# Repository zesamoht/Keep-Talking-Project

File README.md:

# Keep-Talking-Project

A physical homage to the game Keep Talking and Nobody Explode

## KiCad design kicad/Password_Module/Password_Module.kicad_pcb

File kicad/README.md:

For Kicad drawings to be used in the physical manufacturing of the PCB

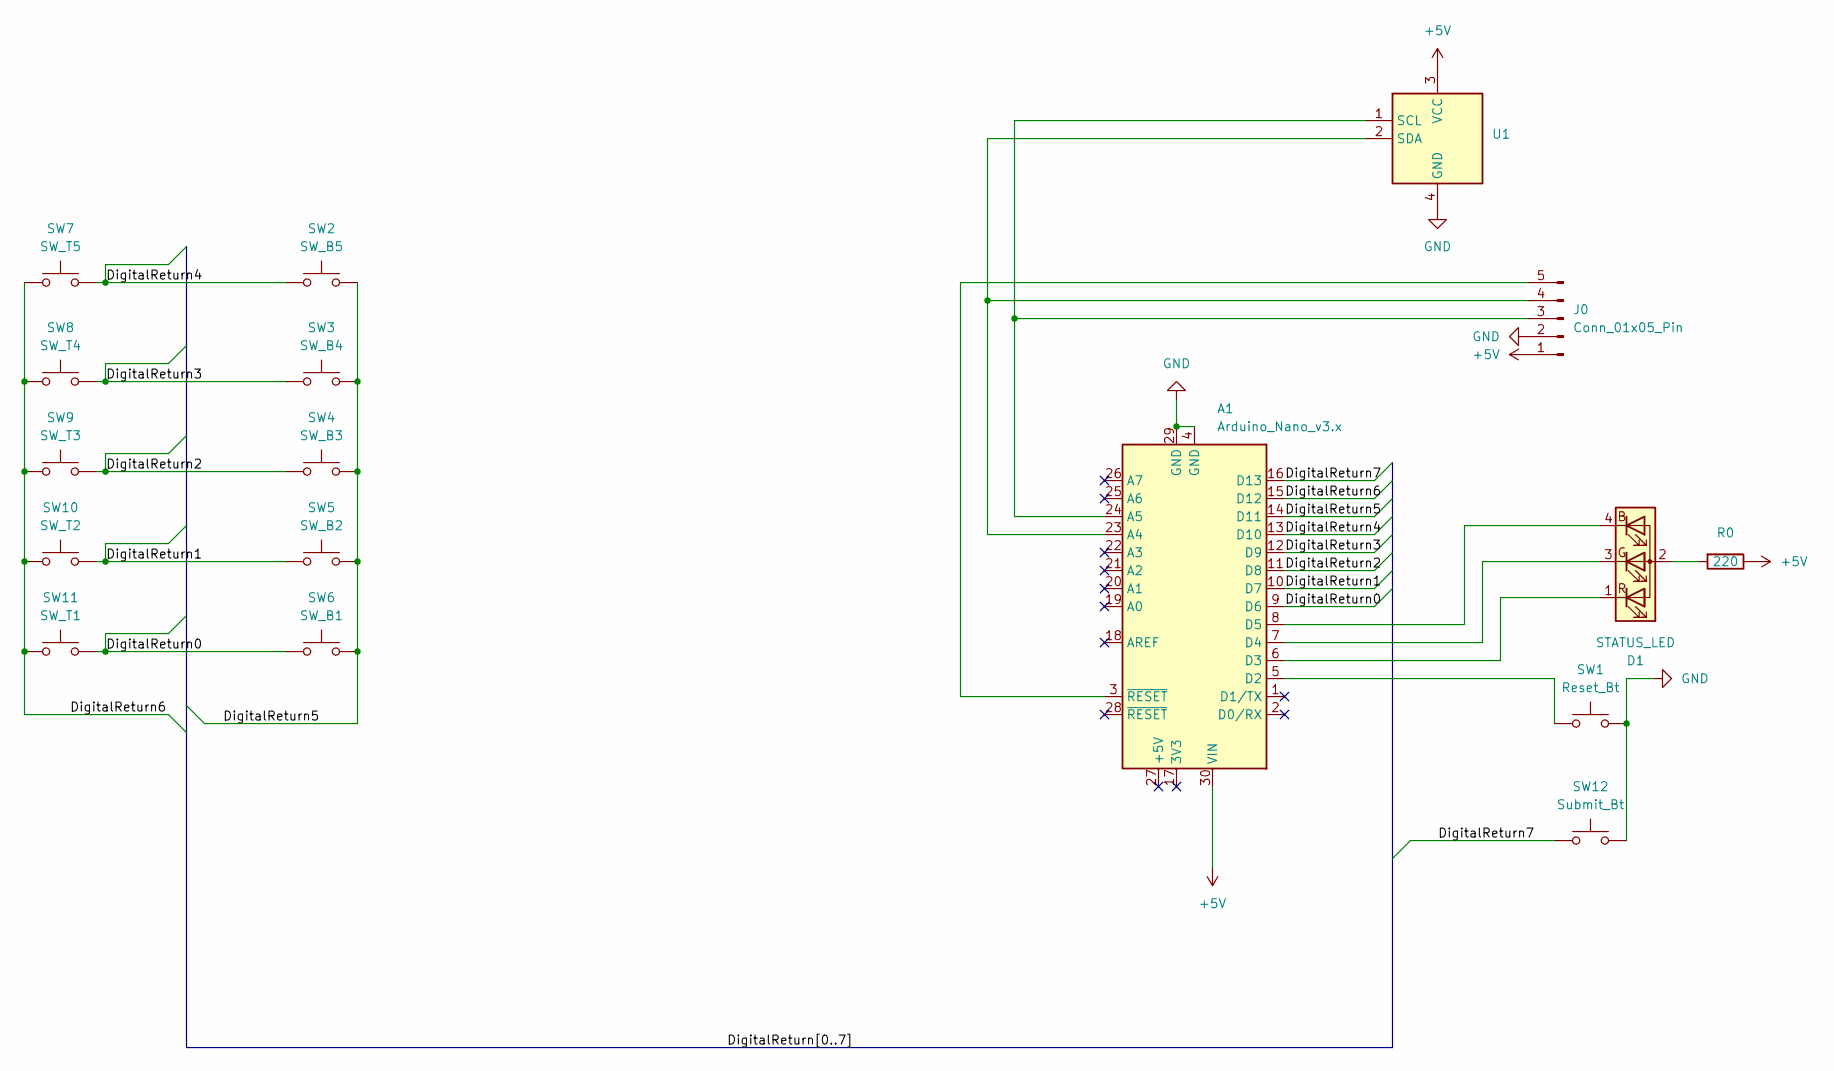
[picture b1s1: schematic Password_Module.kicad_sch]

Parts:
A1: Arduino_Nano_v3.x; Arduino_Nano
D1: STATUS_LED; LED_D5.0mm-4_RGB_Staggered_Pins
J0: Conn_01x05_Pin; JST_XH_B5B-XH-A_1x05_P2.50mm_Vertical
R0: 220; R_Axial_DIN0207_L6.3mm_D2.5mm_P7.62mm_Horizontal
SW1: Reset_Bt; SW_PUSH_6mm_H13mm
SW2: SW_B5; SW_PUSH_6mm_H13mm
SW3: SW_B4; SW_PUSH_6mm_H13mm
SW4: SW_B3; SW_PUSH_6mm_H13mm
SW5: SW_B2; SW_PUSH_6mm_H13mm
SW6: SW_B1; SW_PUSH_6mm_H13mm
SW7: SW_T5; SW_PUSH_6mm_H13mm
SW8: SW_T4; SW_PUSH_6mm_H13mm
SW9: SW_T3; SW_PUSH_6mm_H13mm
SW10: SW_T2; SW_PUSH_6mm_H13mm
SW11: SW_T1; SW_PUSH_6mm_H13mm
SW12: Submit_Bt; SW_PUSH_6mm_H13mm
U1: LCD I2C 8x2 (PCF8574T) I2C

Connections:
+5V: A1.30 (VIN), J0.1, R0.1, U1.3 (VCC)
/DigitalReturn0: A1.9 (D6), SW6.2, SW11.2
/DigitalReturn1: A1.10 (D7), SW5.2, SW10.2
/DigitalReturn2: A1.11 (D8), SW4.2, SW9.2
/DigitalReturn3: A1.12 (D9), SW3.2, SW8.2
/DigitalReturn4: A1.13 (D10), SW2.2, SW7.2
/DigitalReturn5: A1.14 (D11), SW2.1, SW3.1, SW4.1, SW5.1, SW6.1
/DigitalReturn6: A1.15 (D12), SW7.1, SW8.1, SW9.1, SW10.1, SW11.1
/DigitalReturn7: A1.16 (D13), SW12.1
GND: A1.4 (GND), A1.29 (GND), J0.2, SW1.2, SW12.2, U1.4 (GND)
unnamed: A1.23 (A4), J0.4, U1.2 (SDA)
unnamed: A1.24 (A5), J0.3, U1.1 (SCL)
unnamed: A1.5 (D2), SW1.1
unnamed: A1.6 (D3), D1.1 (RK)
unnamed: A1.7 (D4), D1.3 (GK)
unnamed: A1.8 (D5), D1.4 (BK)
unnamed: D1.2 (A), R0.2
unnamed: A1.3 (~RESET), J0.5

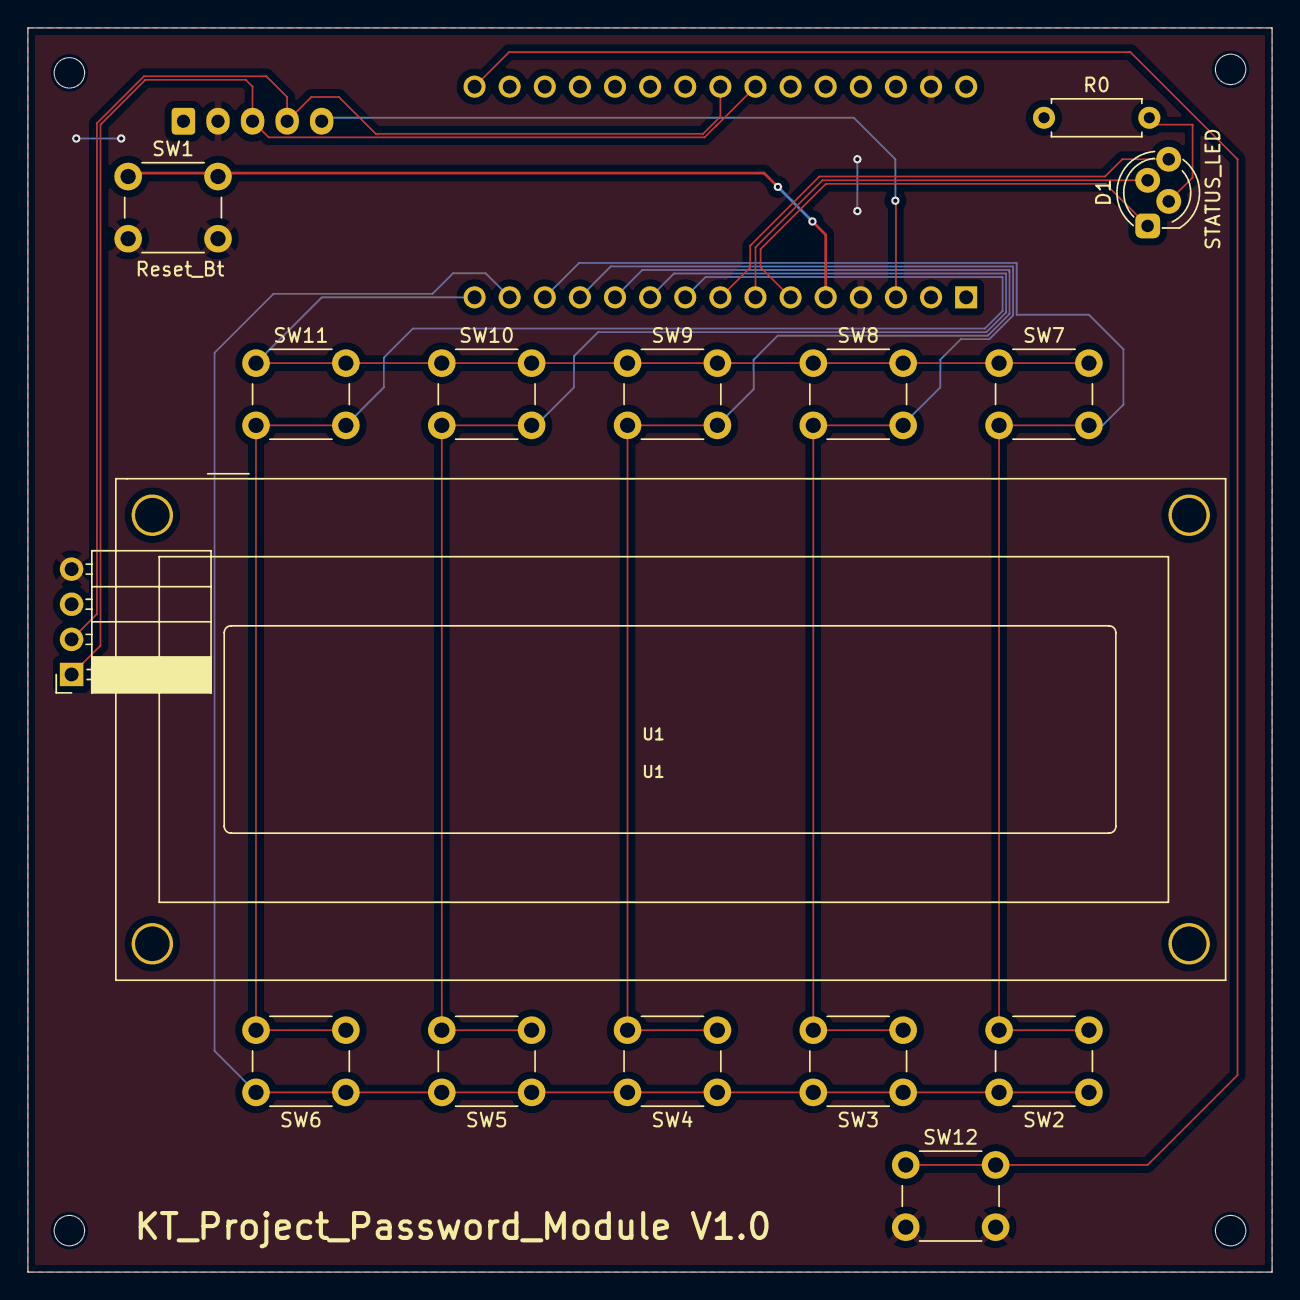
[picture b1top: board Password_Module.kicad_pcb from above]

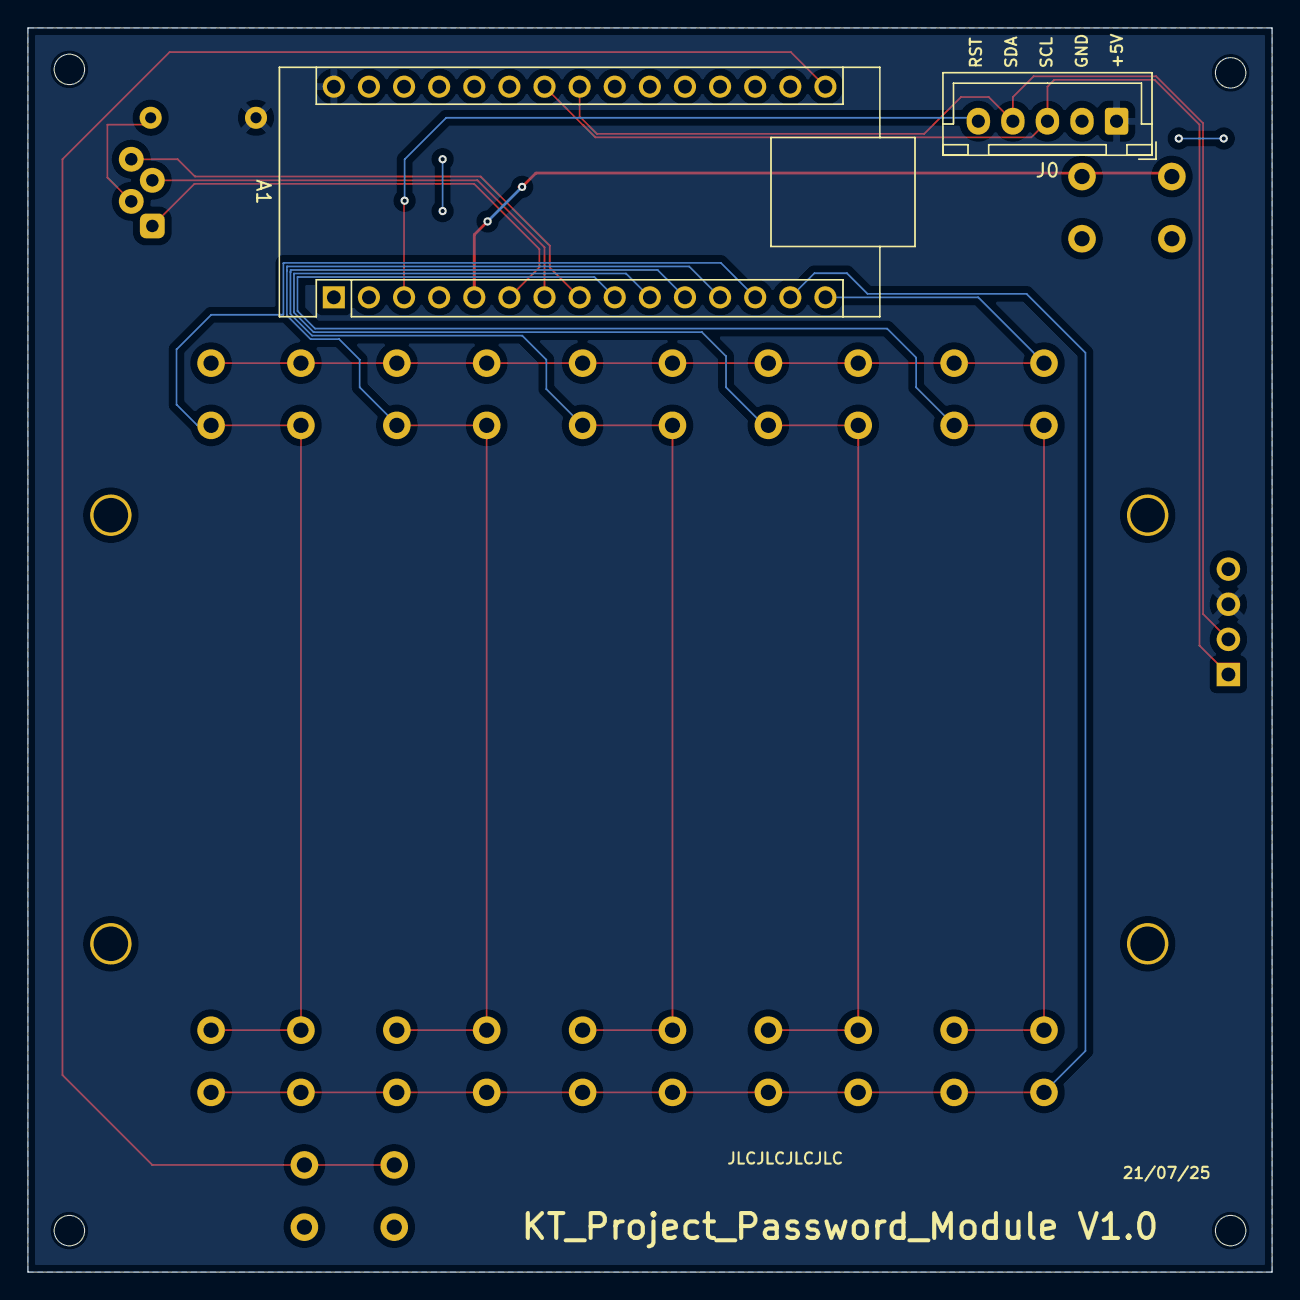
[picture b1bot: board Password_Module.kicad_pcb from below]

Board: 2 copper layers, 90.0 x 90.0 mm, 17 parts (2 on the bottom side), 18 nets.

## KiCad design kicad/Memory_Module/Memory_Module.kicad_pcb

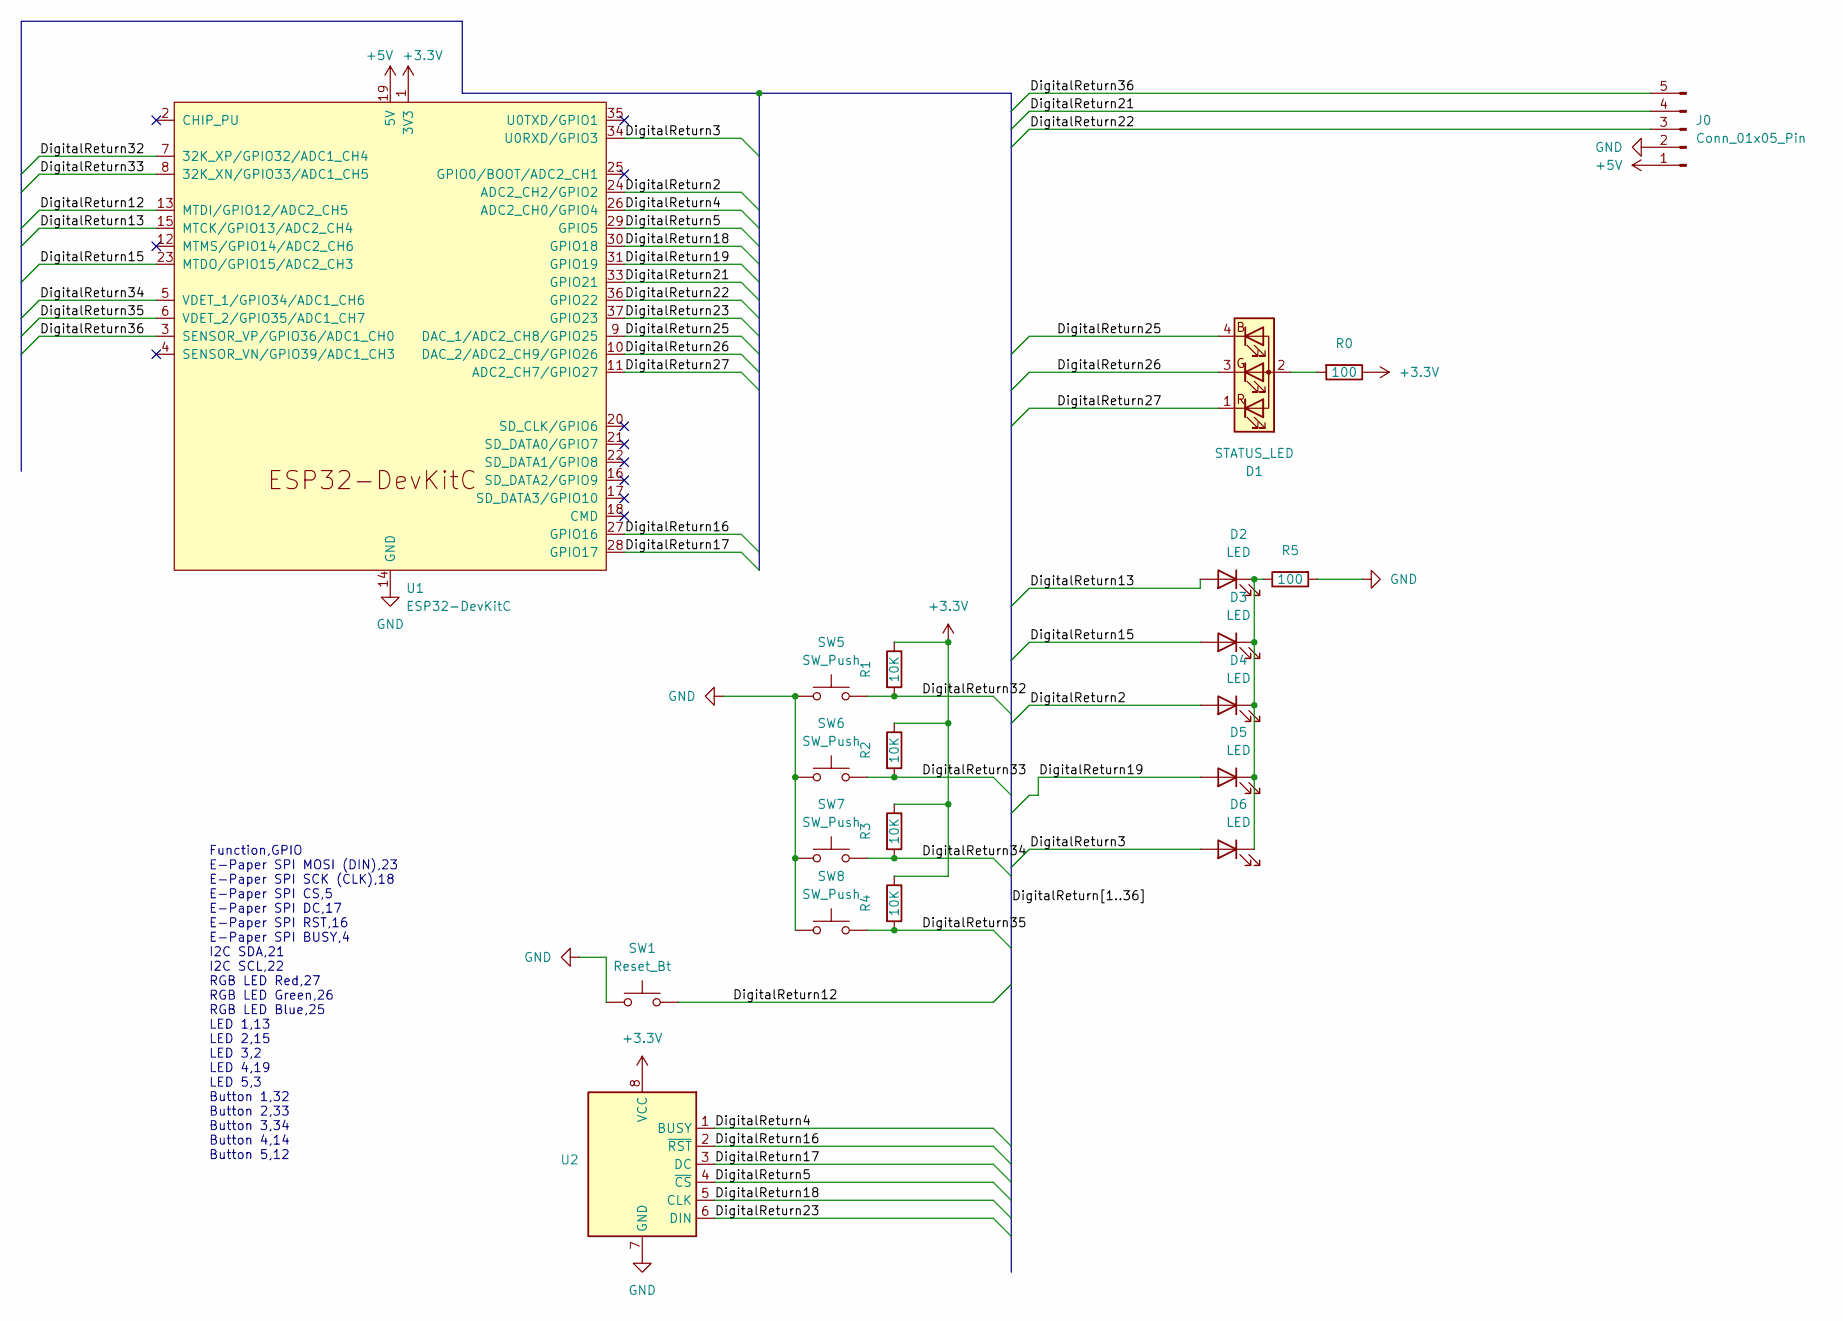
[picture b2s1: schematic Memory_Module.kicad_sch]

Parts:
D1: STATUS_LED; LED_D5.0mm-4_RGB_Staggered_Pins
D2, D3, D4, D5, D6: LED; LED_D5.0mm
J0: Conn_01x05_Pin; JST_XH_B5B-XH-A_1x05_P2.50mm_Vertical
R0, R5: 100; R_Axial_DIN0207_L6.3mm_D2.5mm_P7.62mm_Horizontal
R1, R2, R3, R4: 10K; R_Axial_DIN0207_L6.3mm_D2.5mm_P7.62mm_Horizontal
SW1: Reset_Bt; SW_PUSH_6mm_H13mm
SW5, SW6, SW7, SW8: SW_Push; SW_PUSH_6mm_H13mm
U1: ESP32-DevKitC
U2: WaveShare_E-Paper_Display_200x200

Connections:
+3.3V: R0.1, R1.1, R2.1, R3.1, R4.1, U1.1 (3V3), U2.8 (VCC)
+5V: J0.1, U1.19 (5V)
/DigitalReturn2: D4.2 (A), U1.24 (ADC2_CH2/GPIO2)
/DigitalReturn3: D6.2 (A), U1.34 (U0RXD/GPIO3)
/DigitalReturn4: U1.26 (ADC2_CH0/GPIO4), U2.1 (BUSY)
/DigitalReturn5: U1.29 (GPIO5), U2.4 (~CS)
/DigitalReturn12: SW1.1, U1.13 (MTDI/GPIO12/ADC2_CH5)
/DigitalReturn13: D2.2 (A), U1.15 (MTCK/GPIO13/ADC2_CH4)
/DigitalReturn15: D3.2 (A), U1.23 (MTDO/GPIO15/ADC2_CH3)
/DigitalReturn16: U1.27 (GPIO16), U2.2 (~RST)
/DigitalReturn17: U1.28 (GPIO17), U2.3 (DC)
/DigitalReturn18: U1.30 (GPIO18), U2.5 (CLK)
/DigitalReturn19: D5.2 (A), U1.31 (GPIO19)
/DigitalReturn21: J0.4, U1.33 (GPIO21)
/DigitalReturn22: J0.3, U1.36 (GPIO22)
/DigitalReturn23: U1.37 (GPIO23), U2.6 (DIN)
/DigitalReturn25: D1.4 (BK), U1.9 (DAC_1/ADC2_CH8/GPIO25)
/DigitalReturn26: D1.3 (GK), U1.10 (DAC_2/ADC2_CH9/GPIO26)
/DigitalReturn27: D1.1 (RK), U1.11 (ADC2_CH7/GPIO27)
/DigitalReturn32: R1.2, SW5.2, U1.7 (32K_XP/GPIO32/ADC1_CH4)
/DigitalReturn33: R2.2, SW6.2, U1.8 (32K_XN/GPIO33/ADC1_CH5)
/DigitalReturn34: R3.2, SW7.2, U1.5 (VDET_1/GPIO34/ADC1_CH6)
/DigitalReturn35: R4.2, SW8.2, U1.6 (VDET_2/GPIO35/ADC1_CH7)
/DigitalReturn36: J0.5, U1.3 (SENSOR_VP/GPIO36/ADC1_CH0)
GND: J0.2, R5.2, SW1.2, SW5.1, SW6.1, SW7.1, SW8.1, U1.14 (GND), U1.32 (GND), U1.38 (GND), U2.7 (GND)
unnamed: D1.2 (A), R0.2
unnamed: D2.1 (K), D3.1 (K), D4.1 (K), D5.1 (K), D6.1 (K), R5.1

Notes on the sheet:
Function,GPIO E-Paper SPI MOSI (DIN),23 E-Paper SPI SCK (CLK),18 E-Paper SPI CS,5 E-Paper SPI DC,17 E-Paper SPI RST,16 E-Paper SPI BUSY,4 I2C SDA,21 I2C SCL,22 RGB LED Red,27 RGB LED Green,26 RGB LED Blue,25 LED 1,13 LED 2,15 LED 3,2 LED 4,19 LED 5,3 Button 1,32 Button 2,33 Button 3,34 Button 4,14 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

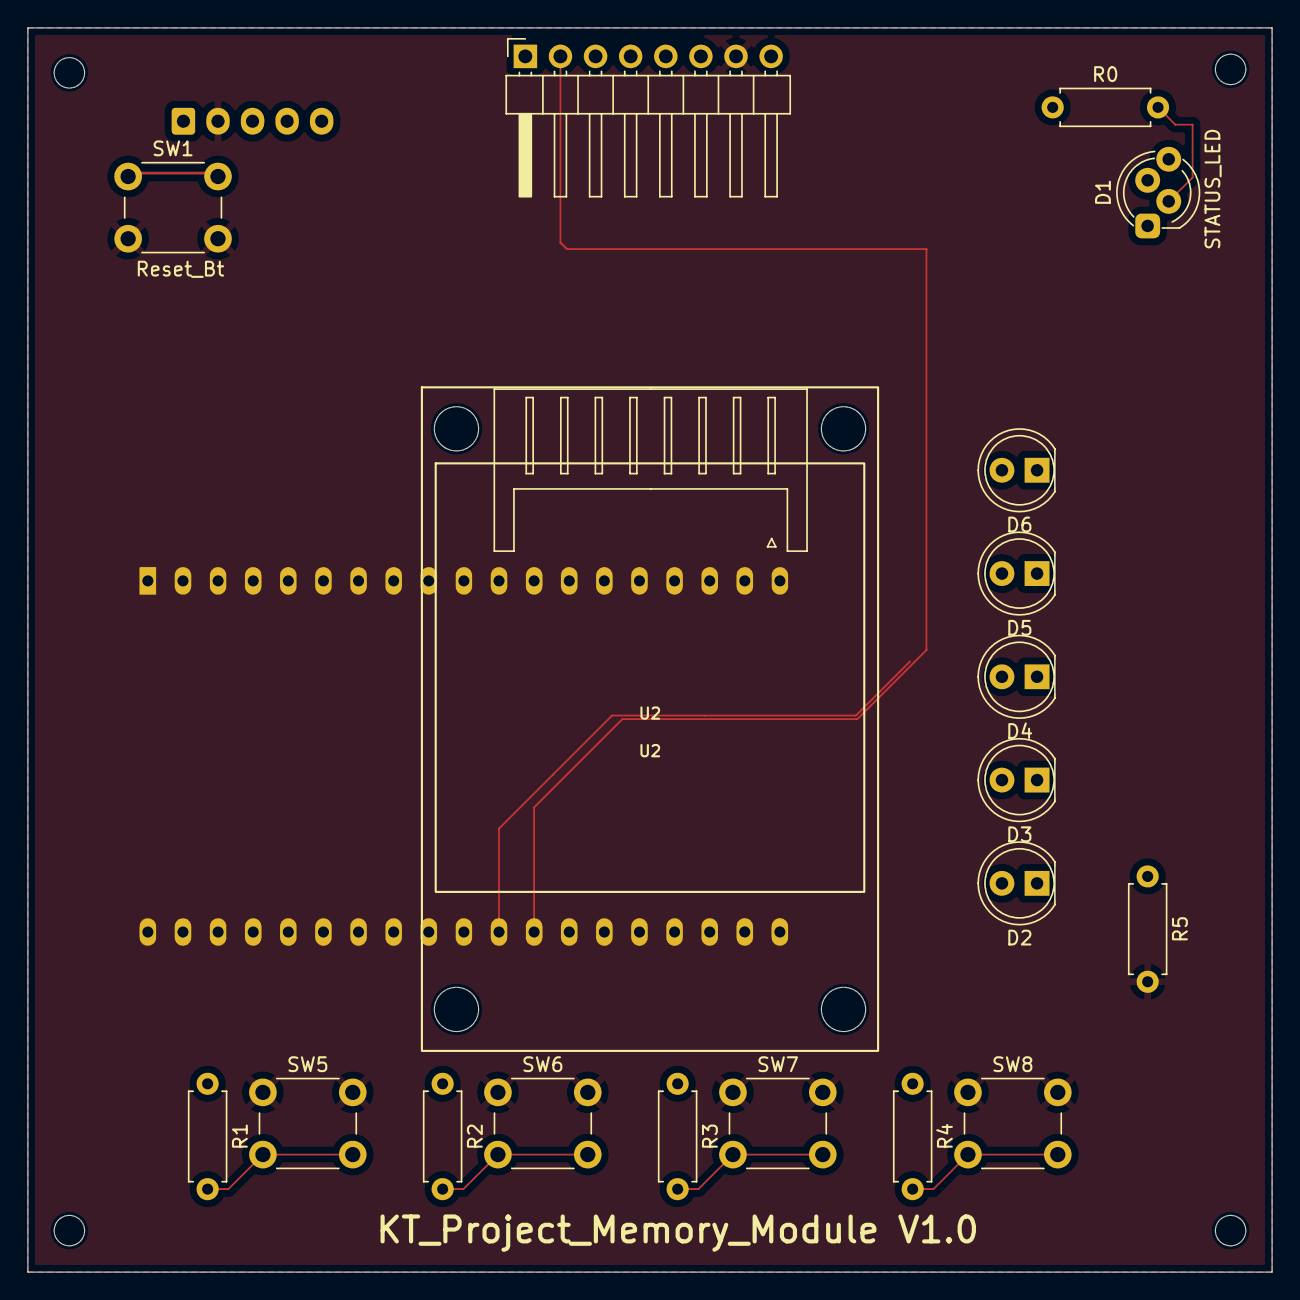
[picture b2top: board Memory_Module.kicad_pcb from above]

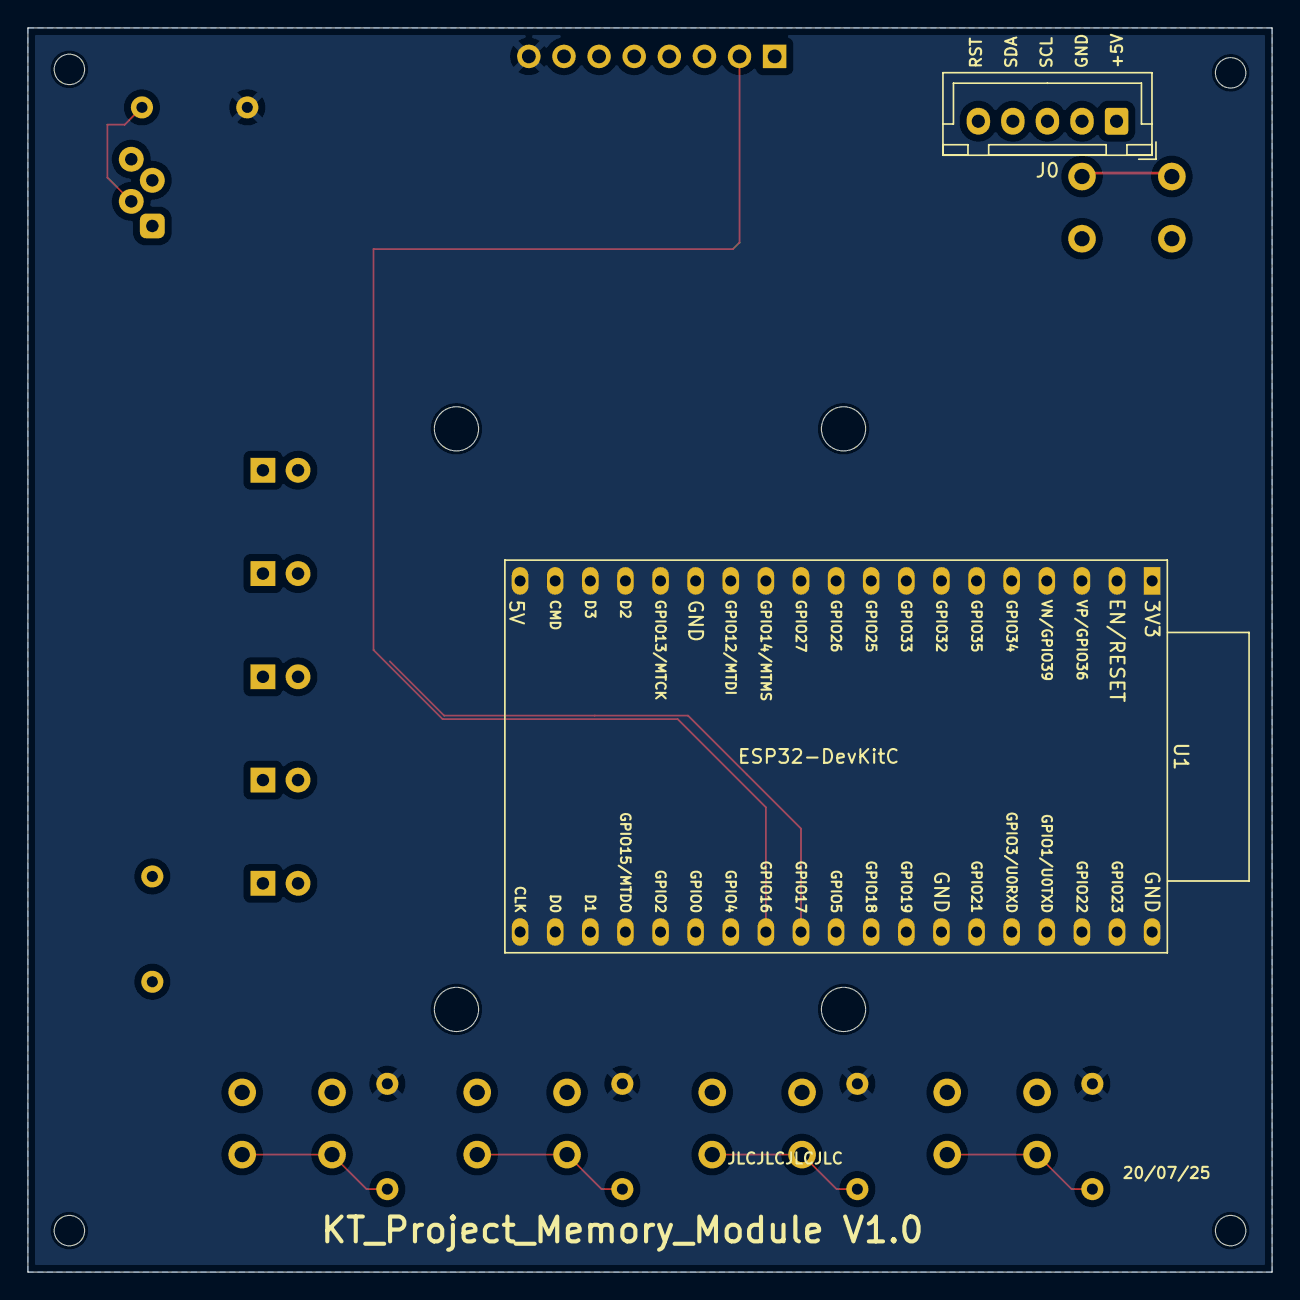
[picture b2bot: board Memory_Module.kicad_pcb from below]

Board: 2 copper layers, 90.0 x 90.0 mm, 20 parts (2 on the bottom side), 27 nets.

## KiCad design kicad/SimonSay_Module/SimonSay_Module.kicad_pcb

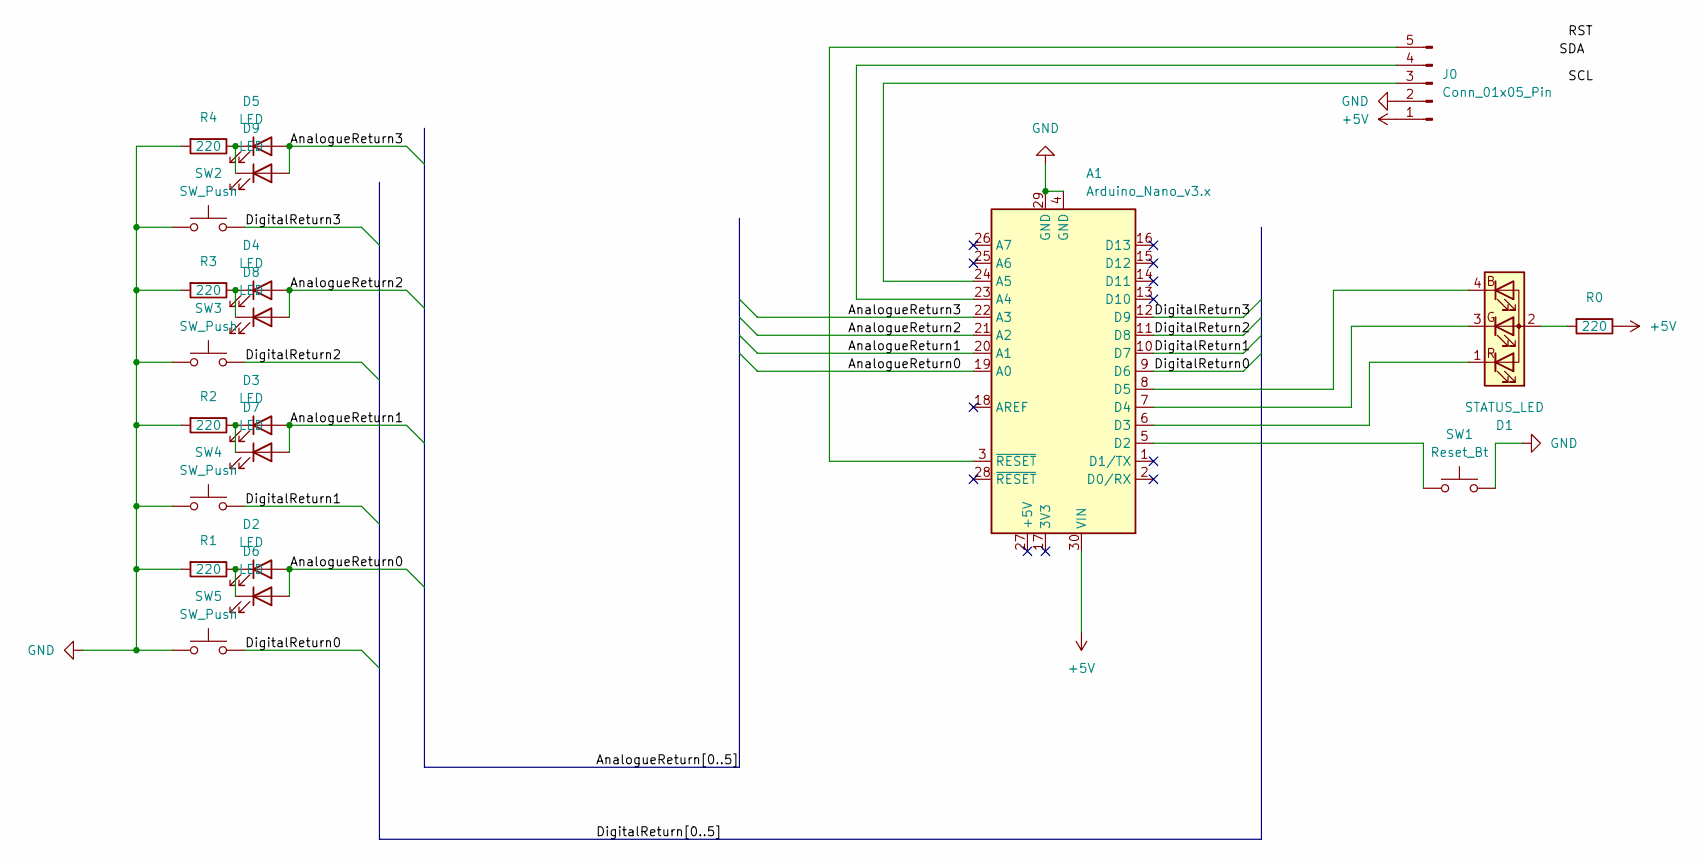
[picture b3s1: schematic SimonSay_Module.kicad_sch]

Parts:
A1: Arduino_Nano_v3.x; Arduino_Nano
D1: STATUS_LED; LED_D5.0mm-4_RGB_Staggered_Pins
D2, D3, D4, D5, D6, D7, D8, D9: LED; LED_D5.0mm
J0: Conn_01x05_Pin; JST_XH_B5B-XH-A_1x05_P2.50mm_Vertical
R0, R1, R2, R3, R4: 220; R_Axial_DIN0207_L6.3mm_D2.5mm_P7.62mm_Horizontal
SW1: Reset_Bt; SW_PUSH_6mm_H13mm
SW2, SW3, SW4, SW5: SW_Push; SW_Cherry_MX_1.00u_Plate

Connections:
+5V: A1.30 (VIN), J0.1, R0.1
/AnalogueReturn0: A1.19 (A0), D2.2 (A), D6.2 (A)
/AnalogueReturn1: A1.20 (A1), D3.2 (A), D7.2 (A)
/AnalogueReturn2: A1.21 (A2), D4.2 (A), D8.2 (A)
/AnalogueReturn3: A1.22 (A3), D5.2 (A), D9.2 (A)
/DigitalReturn0: A1.9 (D6), SW5.2
/DigitalReturn1: A1.10 (D7), SW4.2
/DigitalReturn2: A1.11 (D8), SW3.2
/DigitalReturn3: A1.12 (D9), SW2.2
GND: A1.4 (GND), A1.29 (GND), J0.2, R1.2, R2.2, R3.2, R4.2, SW1.2, SW2.1, SW3.1, SW4.1, SW5.1
unnamed: A1.23 (A4), J0.4
unnamed: A1.24 (A5), J0.3
unnamed: A1.5 (D2), SW1.1
unnamed: A1.6 (D3), D1.1 (RK)
unnamed: A1.7 (D4), D1.3 (GK)
unnamed: A1.8 (D5), D1.4 (BK)
unnamed: D1.2 (A), R0.2
unnamed: D2.1 (K), D6.1 (K), R1.1
unnamed: D3.1 (K), D7.1 (K), R2.1
unnamed: D4.1 (K), D8.1 (K), R3.1
unnamed: D5.1 (K), D9.1 (K), R4.1
unnamed: A1.3 (~RESET), J0.5

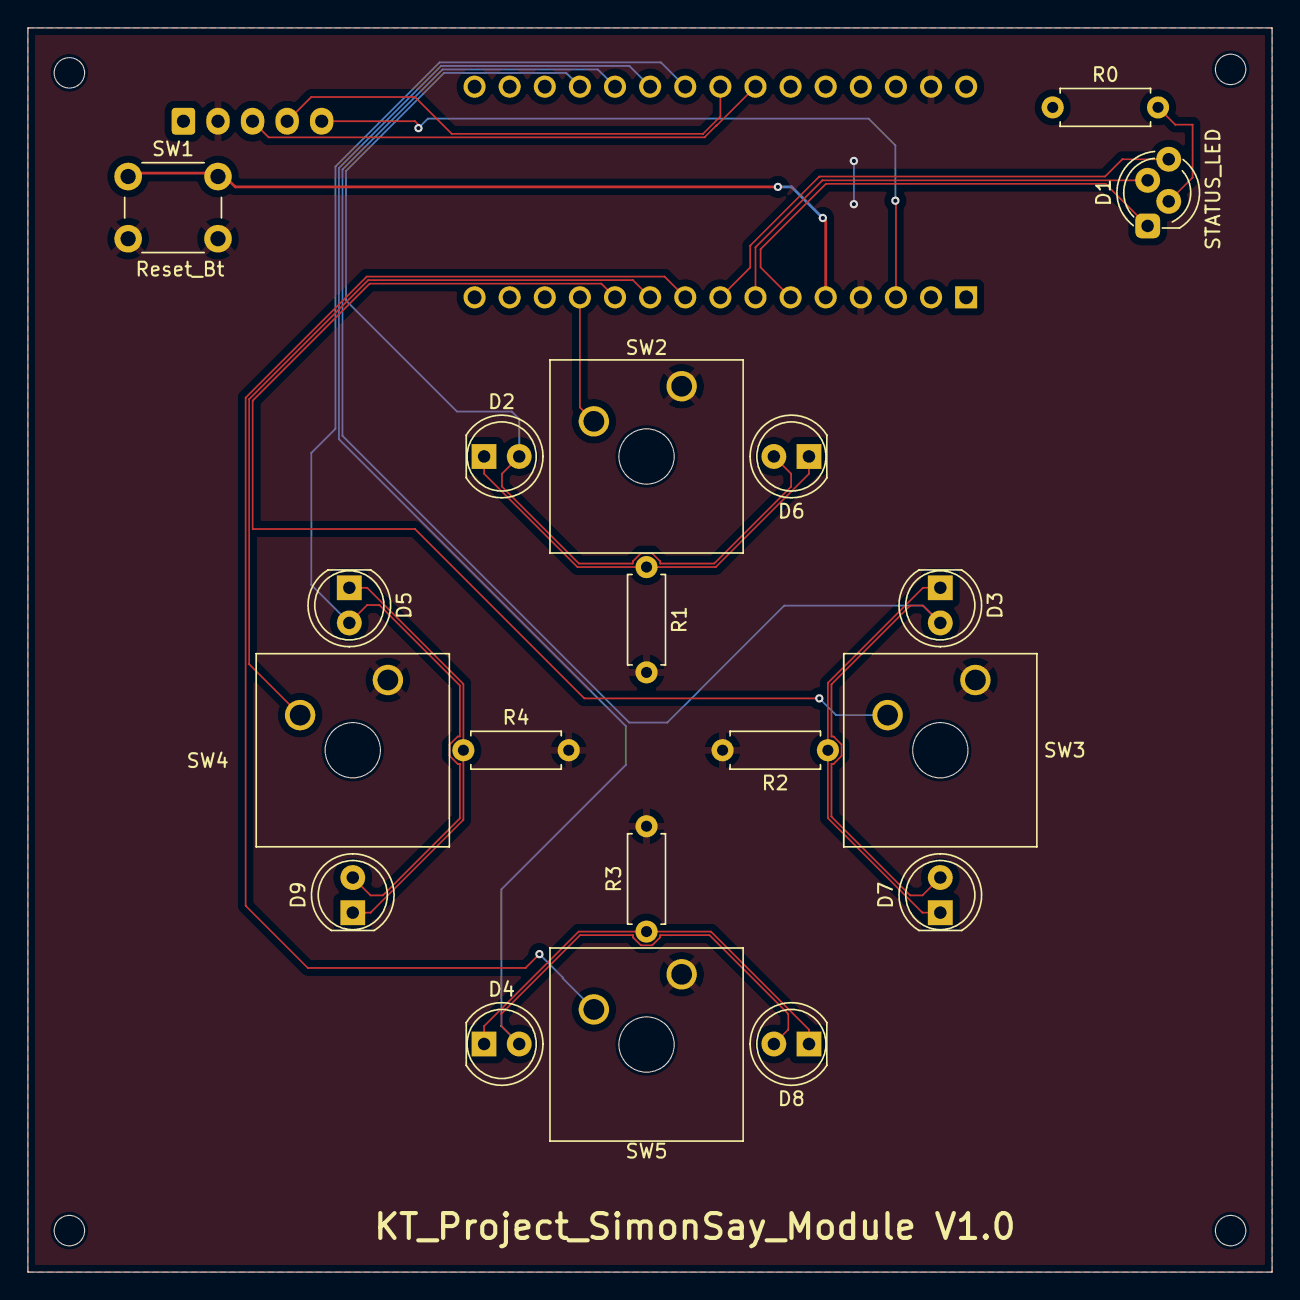
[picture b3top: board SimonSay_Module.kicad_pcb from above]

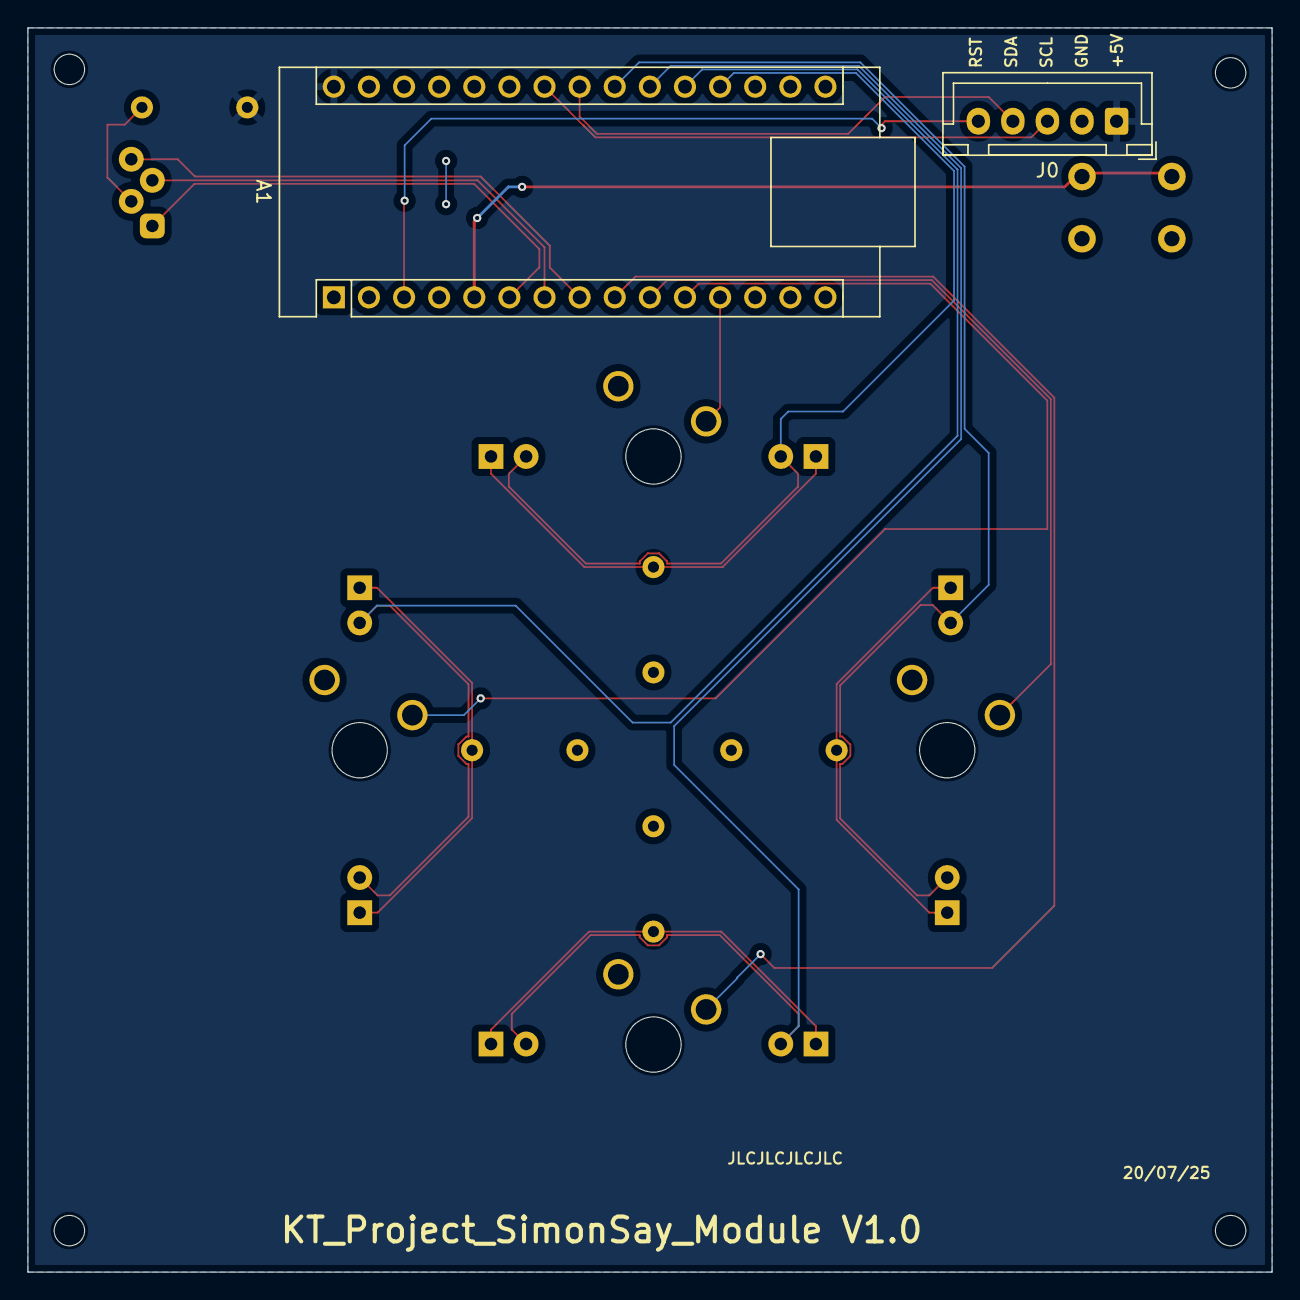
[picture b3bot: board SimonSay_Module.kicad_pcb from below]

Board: 2 copper layers, 90.0 x 90.0 mm, 21 parts (2 on the bottom side), 22 nets.
